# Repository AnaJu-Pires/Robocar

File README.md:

# Robocar Blitz

Carrinho autônomo seguidor de linha para a **RoboCar Race 2026, categoria Micro**. A pista tem linha preta de 20 mm sobre tapete claro, cruzamentos, interseções e bifurcações, e curvas de raio mínimo de 100 mm. Ao fim da volta, o robô tem de parar sozinho no box.
Inspeção e treino em **04/12/2026**; torneio em **05/12/2026** (SENAC Santo Amaro, São Paulo).

**Arquitetura:** câmera IMX219-160 → **Jetson Nano 4 GB** (visão + controle, Python) → USB serial → **ESP32** (PWM, encoders, bateria, largada, watchdog) → 2× DRV8833 → 2× N20 6 V (em 7,2 V). Detalhes em [docs/02_arquitetura.md](docs/02_arquitetura.md).

## Estado (09/11/2026)

| Parte | Situação |
|---|---|
| Software da Jetson | Implementado; **35 testes automáticos passando no PC**; integração com ESP32 **simulada** OK. Não testado na câmera real |
| Firmware da ESP32 | Implementado; **só checagem de sintaxe**, falta compilar e gravar |
| Hardware | Compras definidas (R$ 694,02 com fretes, dentro dos R$ 800); **pedidos a fazer** |
| Placa da ESP32 | **v0.8 espelhada** (motor esquerdo à esquerda, direito à direita; ESP32 no meio, USB para trás): 80 × 73 mm com furos M3 nos cantos, face simples (só B.Cu, sem vias), trilhas de 1,0/1,5 mm com gotas, **3 jumpers**; DRC 0 violações e paridade esquema × placa OK (`make drc`); **falta comprar barras fêmea e fenolite** ([lista de soldagem](hardware/placa_esp32/LISTA_DE_SOLDAGEM.md)), medir as peças, corroer e montar; chassi ainda na v0.7 ([hardware/placa_esp32/](hardware/placa_esp32/)) |
| Mecânica | **Chassi v4, 3 andares — é o que vamos cortar** (D-037): MDF 3 mm, 2 chapas de 390 × 270 mm, **176 × 143 × 181 mm** (162 mm com a câmera em 45°; furos de fixação gravados para furar à mão; luz em cima da câmera); XL4016 e bateria no piso, Jetson no 2º andar (portas para trás), ESP32 no 3º; 51 verificações automáticas (`make chassi`); curva R100 a no máximo 0,80 m/s (D-032); **cortar o pente primeiro** e conferir as medidas estimadas ([mecanica/chassi_v4/](mecanica/chassi_v4/)). Botão de desligar com LED ([hardware/placa_desligar/](hardware/placa_desligar/)) |

Próximos passos e cronograma: [docs/07_plano.md](docs/07_plano.md).

## Início rápido

```bash
make ajuda                      # lista os comandos
make testes                     # testes automáticos (PC ou Jetson; sem hardware)
make calibrar                   # na Jetson: calibração preto/branco
make visao                      # na Jetson: câmera ao vivo, sem mover motores
make carro PORTA=/dev/ttyUSB0   # no carro: largada pelo botão da ESP32
```
Instalação na Jetson: [jetson/README.md](jetson/README.md). Gravação da ESP32: [firmware/README.md](firmware/README.md).

## Onde está cada coisa

| Quero… | Vá para |
|---|---|
| entender a regra e o que perguntar à organização | [docs/01_regulamento.md](docs/01_regulamento.md) |
| ver componentes, elétrica, **pinagem**, massa e cálculos | [docs/03_hardware.md](docs/03_hardware.md) |
| entender ou alterar o código | [docs/04_software.md](docs/04_software.md) · [jetson/](jetson/) |
| ver o esquemático e a placa (PCB) da ESP32 | [hardware/placa_esp32/](hardware/placa_esp32/) |
| cortar e montar o chassi, fiação, inspeção | [mecanica/chassi_v4/](mecanica/chassi_v4/) |
| ver o protocolo Jetson ↔ ESP32 | [docs/05_protocolo_serial.md](docs/05_protocolo_serial.md) |
| testar (bancada e pista) e registrar resultados | [docs/06_testes.md](docs/06_testes.md) |
| comprar / ver orçamento e fretes | [compras/README.md](compras/README.md) |
| saber por que algo foi decidido | [docs/decisoes.md](docs/decisoes.md) |
| contribuir (convenções, git, checklist) | [CONTRIBUTING.md](CONTRIBUTING.md) |
| ver o código original | [legado/](legado/) |

```
docs/        documentação numerada + decisões + regulamento (PDF)
compras/     planilha de compras + CSV original
jetson/      software da Jetson: programas, biblioteca robocar/, config/, testes/
firmware/    firmware da ESP32 (Arduino)
hardware/    placa da ESP32 (KiCad: esquemático, PCB, arquivos de fabricação)
dados/       vídeos, logs e capturas dos testes (fora do git)
legado/      peb.py e seguir_linha.py originais, intactos
```

## Implementado
- Captura de baixa latência (GRAY8 no hardware, fila de 1 quadro, 60 fps, alternativas automáticas).
- Calibração salva em arquivo, com modo automático; limiar adaptativo à iluminação.
- Detecção por faixas que mantém a linha em cruzamentos e interseções em X; erro perto, erro longe e inclinação.
- Controle PD com antecipação e redução de velocidade em curva; busca e parada com linha perdida; parada opcional por marca.
- Protocolo serial versionado com checksum; firmware com estados, watchdog em dois níveis, rampa, encoders, bateria e botão de largada.
- Parâmetros com fonte única e validação; log CSV, gravação de vídeo e reprocessamento offline; Makefile; testes.

## Falta
- [ ] Compras, montagem e chassi.
- [ ] Compilar e testar o firmware; validar encoders, ADC e sentido dos motores.
- [ ] Testar a câmera real: modo, campo de visão, exposição, **latência**, tempo na Jetson.
- [ ] Controle de velocidade com encoder (PI na ESP32, protocolo v2).
- [ ] Ajustar ganhos e velocidades na pista de teste; definir a detecção do box conforme a resposta da organização.
- [x] Início automático no boot (`make servico`, em `jetson/servico/`). Falta testar na Jetson.
- [ ] Desligamento seguro sem SSH.

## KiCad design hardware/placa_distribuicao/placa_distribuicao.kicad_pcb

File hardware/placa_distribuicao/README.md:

# Placa de distribuição de energia (fusível, chave e saídas), 32 × 44 mm, face simples

Substitui a placa improvisada de cobre dividido. É a **mesma ideia** (cobre grande, fios soldados direto no cobre),
mas com 4 ilhas na ordem certa, um diodo de proteção e um LED de "chave ligada". Fica no **andar 2**, atrás da Jetson,
entre o plugue USB e o P4, em **2 espaçadores M3 de 10 mm**. Decisão: [D-036](../../docs/decisoes.md).

**Abrir no KiCad:** Arquivo → Abrir projeto → `hardware/placa_distribuicao/placa_distribuicao.kicad_pro`. Na janela
do projeto: esquemático (`placa_distribuicao.kicad_sch`) e placa (`placa_distribuicao.kicad_pcb`); na placa, **Alt+3**
abre o 3D. Abre no KiCad 7 a 10. O 3D também está em `placa_distribuicao.step` (abre no Onshape/FreeCAD). O
esquemático é conferido pelo próprio KiCad contra o circuito e contra a placa a cada `make placa-distribuicao`.

## Circuito

```
 XT60 (bateria) ── BAT+ ──[ F1 7 A ]── FUS+ ── fio ──► chave KCD1 (terminal 1)
                                                      chave KCD1 (terminal 2) ── fio ──► SW+
 SW+ ──► XL4016 #1 (Jetson)      um par de fios só para ele
     ──► XL4016 #2 (motores)     um par de fios só para ele
     ──► VBAT (fio fino até o J1 da placa da ESP32: medir a bateria)
     ──► R1 4,7 kΩ ──► LED verde ──► GND           aceso = chave ligada (puxa ~2 mA)
     ──┤◄── D1 1N5408 ── GND                       proteção contra bateria invertida
 XT60 (bateria) ── BAT− ── GND ──► XL4016 #1 −, XL4016 #2 −
```

| Ilha | Liga em | Fica |
|---|---|---|
| **BAT+** | + da bateria (pigtail do XT60) e um lado do fusível | trás, lado direito |
| **FUS+** | outro lado do fusível e o fio para o terminal 1 da chave | trás, lado esquerdo (perto da chave) |
| **SW+** | fio que volta do terminal 2 da chave; saídas XL1+, XL2+, VBAT; LED; catodo do D1 | frente, lado esquerdo |
| **GND** | − da bateria; XL1−, XL2−; LED; anodo do D1 | frente, lado direito |

## Por que assim (decisões)

| Pergunta | Decisão | Por quê |
|---|---|---|
| Ordem | **bateria → fusível → chave → conversores** | o fusível protege tudo a partir da bateria, inclusive o fio da chave. A placa improvisada não deixava claro onde a chave entrava |
| Como alimentar os 2 XL4016 | **um par de fios para cada um**, saindo da placa (em estrela) | antes o #2 pegava energia no borne do #1 (2 fios por borne). Com isso a corrente dos motores passava pelo borne e pelo fio da Jetson: quando os motores arrancavam, a entrada da Jetson também caía. Em estrela, cada um tem o seu fio |
| VBAT | **sai da placa** (ilha SW+), não emendado no terminal da chave | menos emenda; mede a bateria depois da chave, como antes |
| Diodo de proteção | **D1 em paralelo (catodo no SW+)**, não em série | em série, ele perderia ~0,5 V e esquentaria o tempo todo. Em paralelo, não faz nada no uso normal. Com a bateria invertida, ele conduz e **queima o fusível** antes de algo estragar (o XT60 já não encaixa invertido; isso cobre um pigtail soldado trocado ou uma fonte de bancada ligada ao contrário). Use **1N5408** (aguenta o pico até o fusível abrir); sem ele, 1N4007 é a segunda opção (pode abrir antes do fusível; aí só não protege) |
| LED verde | **aceso = chave ligada** | a Jetson desligada não mostra nada, e a bateria ligada com a chave esquecida em ON descarrega a LiPo abaixo do limite. O LED denuncia |
| Cobre | 4 ilhas grandes, **≥ 3 mm de largura em todo caminho** de corrente, pinos ligados **direto** (sem alívio térmico) | 7 A (fusível) em cobre de 35 µm pede ~2,5 mm (IPC-2221); 3 mm dá margem para a corrosão caseira. Ligação direta = mais corrente, como na placa improvisada (precisa de ferro de 40 W ou mais) |
| Sem letras no cobre | os nomes ficam na **folha de montagem** | letras de cobre partiam as ilhas no meio |
| Fixação | **2 parafusos M3 + espaçadores de 10 mm** | os fios são soldados por baixo: precisam de espaço até o MDF. Os furos ficam no vão entre as ilhas, com 3,6 mm sem cobre em volta (o parafuso não encosta em nenhuma ilha) |

## Peças (todas da lista de compras, exceto D1, LED e R1, do laboratório)

> **NUNCA use 1N4728 no D1.** O 1N4728 é um **zener de 3,3 V**, não um diodo retificador. No lugar do D1 ele
> conduz com qualquer tensão acima de 3,3 V: com a bateria (11–12,6 V) vira um **curto**, e o fusível queima (ou o
> zener esquenta até estourar) assim que a chave liga. Sem 1N5408 ou 1N400x, deixe o D1 vazio: a placa funciona igual,
> só sem a proteção contra bateria invertida (o XT60 já não encaixa ao contrário).

| Ref | Peça | Item da lista |
|---|---|---|
| F1 | fusível de vidro **5 × 20 mm 7 A** + 2 **terminais porta-fusível 5 × 20** (clipes para soldar) | 14 e 15 |
| — | chave gangorra **KCD1-101 2T** (na parede do berço da bateria, não na placa) | 16 |
| D1 | diodo **1N5408** (ou 1N4007; ver acima). **Sem eles, deixe o D1 vazio.** | laboratório / ~R$ 0,50 |
| D2 | LED verde 3 mm | laboratório |
| R1 | resistor 4,7 kΩ (3,3k a 10k servem) | laboratório |
| — | cabinho 0,75 mm² vermelho e preto | 19 e 20 |
| — | 2 espaçadores M3 de 10 mm + 2 parafusos M3 × 16 + porcas | 23 |
| — | placa de fenolite face simples, 32 × 44 mm (sobra da placa da ESP32) | — |

**Antes de corroer:** imprima `fabricacao/1_cobre_transferencia_1x1.pdf` em 100 % (sem "ajustar à página"), meça a
largura da placa no papel com régua (**32,0 mm**) e ponha os 2 clipes do fusível em cima do desenho. Os furos dos
clipes estão para clipes com pinos externos a **20 mm** (Littelfuse 111). Se os seus forem diferentes, me passem a
medida.

## Fazer

1. Corrosão: igual à placa da ESP32 (`1_cobre_transferencia_1x1.pdf`, preto = cobre, marca no centro de cada furo).
2. Furos: fios grossos 1,5 mm; clipes do fusível e D1 1,0–1,3 mm (confira na peça); R1, LED e VBAT 0,8–1,0 mm;
   fixação 3,2 mm. Mapa em `fabricacao/*.drl`.
3. Montagem pela [folha de montagem](fabricacao/2_montagem.pdf): clipes do fusível, D1 (**faixa no lado do SW+**),
   R1, LED (**perna longa no furo de cima, que vai ao R1**), fios por último.
4. **Antes de pôr a bateria**, multímetro em continuidade:
   * BAT+, FUS+, SW+ e GND **sem continuidade entre si** (sem o fusível);
   * com o fusível: BAT+ ↔ FUS+ em continuidade;
   * chave ligada: FUS+ ↔ SW+ em continuidade; desligada: aberto.
5. Bateria, chave desligada: LED apagado, 0 V nos XL4016. Chave ligada: LED aceso, tensão da bateria nos 2 XL4016.

## Fios (comprimentos de corte do modelo do chassi; ver `mecanica/chassi_v4/verificacao.md`)

| Fio | De → para | Corte |
|---|---|---|
| pigtail (vermelho + preto) | XT60 do chassi → BAT+ / BAT− | 132 mm |
| vermelho | CHAVE 1 → terminal 1 da chave | 92 mm |
| vermelho | terminal 2 da chave → CHAVE 2 | 93 mm |
| par | XL1 + / XL1 − → IN do XL4016 #1 (Jetson) | 151 mm |
| par | XL2 + / XL2 − → IN do XL4016 #2 (motores) | 145 mm |
| fino | VBAT → J1 da placa da ESP32 | 177 mm (Dupont de 1 via no meio, para tirar o andar 3) |

Os pares dos XL4016 descem pelo passa-fio novo na frente da placa (andar 2) e passam por cima dos motores.

## Gerar de novo

```bash
make placa-distribuicao
```

Roda `placa.py` (Python do KiCad): monta a placa, roda o DRC (cobre, furos, bordas, corpos, ligações), confere pino a
pino contra o circuito, confere que só há cobre embaixo e que todo caminho de corrente tem ≥ 3 mm, e grava o
`.kicad_pcb`, os PDFs 1:1, a furação e as imagens. `python3 placa.py --negativos` planta 8 defeitos (um deles, um esquemático com o diodo invertido) e confere
que cada um é pego.

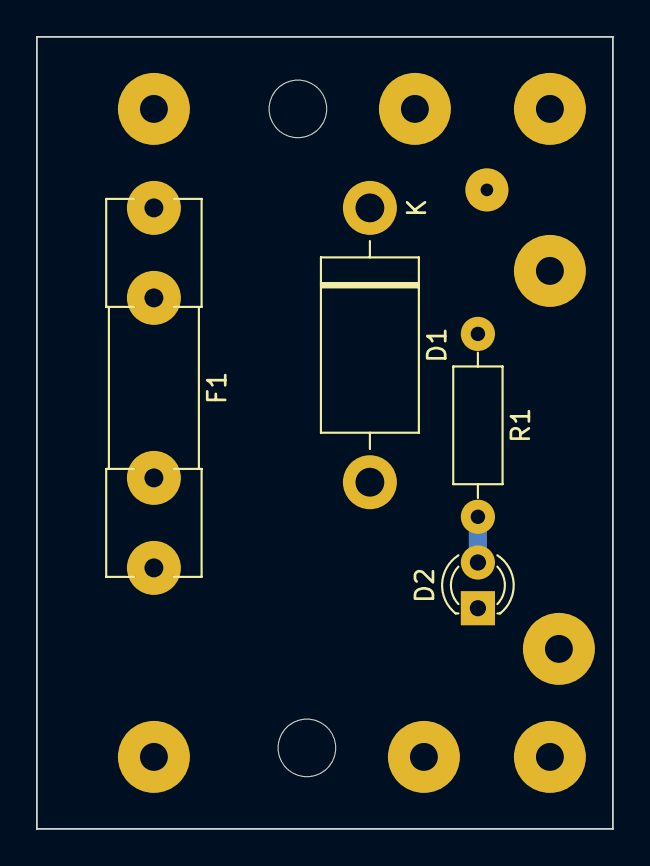
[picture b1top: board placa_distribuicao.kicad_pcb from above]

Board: 2 copper layers, 32.0 x 44.0 mm, 15 parts (0 on the bottom side), 5 nets.

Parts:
D1: D_DO-201AD_P15.24mm_Horizontal
D2: LED_D3.0mm
F1: Fuseholder_Clip-5x20mm_Littelfuse_111_Inline_P20.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; Fuseholder_Clip-5x20mm_Littelfuse_111_Inline_P20.00x5.00mm_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
H1, H2: MountingHole_3.2mm_M3
J_BATN: SolderWire-0.75sqmm_1x01_D1.25mm_OD2.3mm
J_BATP: SolderWire-0.75sqmm_1x01_D1.25mm_OD2.3mm
J_CH1, J_CH2: SolderWire-0.75sqmm_1x01_D1.25mm_OD2.3mm
J_VBAT: SolderWire-0.127sqmm_1x01_D0.48mm_OD1mm
J_XL1N, J_XL1P, J_XL2N, J_XL2P: SolderWire-0.75sqmm_1x01_D1.25mm_OD2.3mm
R1: R_Axial_DIN0207_L6.3mm_D2.5mm_P10.16mm_Horizontal

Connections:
BAT+: F1.2, J_BATP.1
FUS+: F1.1, J_CH1.1
GND: D1.2, D2.1, J_BATN.1, J_XL1N.1, J_XL2N.1
LED: D2.2, R1.2
SW+: D1.1, J_CH2.1, J_VBAT.1, J_XL1P.1, J_XL2P.1, R1.1

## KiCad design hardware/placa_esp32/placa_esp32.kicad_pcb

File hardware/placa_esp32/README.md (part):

# Robocar Blitz — placa da ESP32, v0.8 (espelhada)

Placa da ESP32 com os dois drivers DRV8833. **Tudo do motor esquerdo fica na metade esquerda da placa e tudo do
motor direito na metade direita**: cada cabo de motor (6 fios) e cada par de VM chega no seu lado. Face simples
(cobre só embaixo), para **corrosão manual**.

* **80 × 73 mm** (vista de cima: borda de cima = frente do carro, borda de baixo = traseira).
* **4 furos M3 nos cantos**, a 3,5 mm das bordas (73 × 66 mm entre centros). Nenhum cobre que não seja GND a menos
  de 3,6 mm do centro de um furo (pode usar espaçador metálico).
* **ESP32 em pé, no meio, com o USB para trás** (borda de baixo) e a antena para a frente. Embaixo da antena **não
  tem cobre** (área proibida no KiCad), como pede a Espressif — mesmo sem a ESP32 usar rádio neste projeto.
* **Ilhas retangulares arredondadas**, maiores só no sentido que não aproxima o pino vizinho (furo e passo das peças
  não mudaram — a ESP32 e os módulos continuam encaixando).
* **Trilhas**: sinal 1,0 mm; potência (VM, GND dos drivers e motores) 1,5 mm. Só 0°/45°/90°, **nenhuma curva de
  90°** (toda curva é chanfrada) e toda trilha **sai reta da ilha**, no sentido do lado comprido dela. Folga mínima
  0,5 mm (0,6 mm no plano de GND).
* **Gotas (teardrops)** em 64 saídas de ilha: o cobre engrossa na junção ilha–trilha (mais resistente ao calor do
  ferro e à corrosão por baixo).
* **Plano de GND** em volta de todas as ilhas; toda ilha de GND chega ao plano com pelo menos 2 raios de alívio
  térmico (sem toco de trilha).
* **3 jumpers de fio** (JP1, JP2 embaixo dos módulos e JP3 do lado do U3). Ver [Jumpers](#jumpers-3).
* Mesmo circuito da v0.7 (mais o JP3); **mudou a pinagem da ESP32** (firmware atualizado, [config.h](../../firmware/robocar_esp32/config.h)).

Lista do que soldar, o que é cada peça e o que já temos: **[LISTA_DE_SOLDAGEM.md](LISTA_DE_SOLDAGEM.md)**.

## O que tem aqui

| Arquivo | Conteúdo |
|---|---|
| `placa_esp32.kicad_pro` / `.kicad_sch` / `.kicad_pcb` | Projeto KiCad (abre no KiCad 10; arquivos no formato do KiCad 7, o KiCad 10 converte ao salvar) |
| `placa_esp32.kicad_dru` | Regras de **face simples** (DRC acusa trilha/zona em F.Cu e via) e as exceções de courtyard (resistores embaixo da ESP32) |
| `ferramentas/montar_placa_v08.py` | **Gera a placa** a partir do esquemático: posições, trilhas, plano, área da antena, gotas e serigrafia (tabelas `POS` e `ROTAS`) |
| `verificar.py` | DRC + "só B.Cu" + ângulos/larguras + distância aos furos + paridade esquema × placa + zona salva (`make drc`) |
| `gerar_saidas.sh` | Refaz PDFs, furação, STEP e imagens (`make placa`) |
| `placa_esp32.pdf` | Esquemático em PDF |
| `placa_esp32.step` | Placa montada em 3D (ESP32 do fabricante; barras fêmea, resistores e capacitores nativos do KiCad) |
| `fabricacao/1_cobre_transferencia_1x1.pdf` | **Arte do cobre**, 1:1 numa folha A4, preto = cobre, marca de centro nas ilhas |
| `fabricacao/2_montagem_e_jumpers.pdf` | Lado dos componentes: peças, referências e os 3 jumpers |
| `fabricacao/*.drl`, `*-drl_map.pdf` | Furação (Excellon) e mapa de brocas |
| `fabricacao/BOM.csv` | Peças com posição |
| `imagens/` | Cobre visto de cima, lado do cobre, folha de montagem e vista 3D |
| `lib/robocar_sm.pretty` | Pegadas `_SoldaManual` (ilhas retangulares arredondadas) |

## Disposição

| Lado ESQUERDO (motor esquerdo) | Meio | Lado DIREITO (motor direito) |
|---|---|---|
| J10 motor E (M+ M−), em cima | R1 + J1 (VBAT), em cima | J11 motor D (M+ M−), em cima |
| U2 = DRV8833 esquerdo | ESP32 (U1), USB para trás | U3 = DRV8833 direito, JP3 ao lado |
| J12 encoder E (A, B, −, +) | R2, R3, R4 embaixo da ESP32 | J13 encoder D (A, B, −, +); J14 largada |
| C1 470 µF + J2 VM E, embaixo | — | C2 470 µF + J3 VM D, embaixo |

* A **coluna esquerda** da ESP32 (pinos 1–15) só atende o motor esquerdo; a **direita** (16–30), o direito.
* Os sinais saem da coluna da ESP32 e sobem até as entradas do módulo (embaixo dele); as saídas (em cima) vão
  para J10/J11. VM e GND do módulo saem por dentro dele e descem pela borda até o 470 µF e o fio do XL4016.
* O 3V3 dos encoders sai do pino 3V3 (embaixo, coluna direita) pelos dois lados da ilha: um ramo vai direto ao J13
  e o outro passa por baixo da ponta USB da ESP32 até o J12.
* No J12/J13 a ordem é **A, B, −, +** (o + ficou na ponta para o 3V3 chegar sem cruzar nada; rótulos na serigrafia).

### Pinagem da ESP32 (igual ao [config.h](../../firmware/robocar_esp32/config.h))

| Pino | GPIO | Função | Vai para |
|---|---|---|---|
| 2 | 36 (VP) | bateria (ADC1) | R1 220k (VBAT) / R2 47k (GND) |
| 6 | 32 | nSLEEP do U2 | EEP do U2; R3 10k para o GND |
| 7 | 33 | motor esquerdo IN1 | IN2+IN4 do U2 (ponte espelhada, [D-013](../../docs/decisoes.md)) |
| 8 | 25 | motor esquerdo IN2 | IN1 do U2 e, pelo JP1, IN3 |
| 9 / 10 | 26 / 27 | encoder esquerdo A / B | J12 |
| 14 / 29 | GND | — | plano de GND |
| 20 | 21 | motor direito IN2 | IN1 do U3 e, pelo JP2, IN3 |
| 21 | 19 | motor direito IN1 | IN2+IN4 do U3 |
| 22 | 18 | nSLEEP do U3 | R4 10k para o GND e, pelo JP3, EEP do U3 |
| 24 / 25 | 17 / 16 | encoder direito A / B | J13 |
| 26 | 4 | largada | J14 (jumper ou botão para o GND) |
| 27 | 2 | LED | LED da própria DevKit |
| 30 | 3V3 | + dos encoders | J12, J13 |

Evitados: 0, 2, 5, 12, 15 (strapping), 1 e 3 (USB serial), 14 (PWM no boot), 39.

## Ligações (fios)

| Ponto | Fio | De onde |
|---|---|---|
| J2 `+ −` (VM E) | cabinho 0,75 mm² vermelho/preto | saída do **XL4016 #2 (7,2 V)** — 1º par |
| J3 `+ −` (VM D) | cabinho 0,75 mm² vermelho/preto | XL4016 #2 — 2º par |
| J10 `M+ M−` | vermelho (M+), branco (M−) | cabo do motor **esquerdo** |
| J12 `A B − +` | amarelo (A), verde (B), azul (−), preto (+) | **mesmo cabo** do motor esquerdo |
| J11 `M+ M−` | vermelho, branco | cabo do motor **direito** |
| J13 `A B − +` | amarelo, verde, azul, preto | mesmo cabo do motor direito |
| J1 `VBAT` | fio fino | + da bateria **depois da chave** |
| J14 | 2 pinos macho + jumper (ou botão em 2 fios) | largada |
| USB da ESP32 | cabo de dados | Jetson (alimenta a ESP32 e conversa com ela) |

Cores do cabo da RoboCore: 1 vermelho M+, 2 branco M−, 3 amarelo A, 4 verde B, 5 preto + do encoder, 6 azul − do
encoder. **Confira com o multímetro** antes de soldar.

## Regras usadas

| Item | Valor | Por quê |
|---|---|---|
| Trilha de sinal | **1,0 mm** | corrente de mA; 1,0 mm aguenta ≈ 2,4 A (IPC-2221, cobre 35 µm, +10 °C) e sobrevive à corrosão manual |
| VM, GND dos drivers, motores | **1,5 mm** | ≈ 3,2 A (IPC-2221, 35 µm, +10 °C) contra 1,9 A de pico (motor travado em 7,2 V): folga de 1,7× |
| Folga cobre–cobre | 0,5 mm (plano: 0,6 mm) | transferência térmica + percloreto |
| Cobre até a borda | ≥ 0,6 mm | |
| Ângulos | só 0°, 45° e 90° de direção; **nenhuma curva de 90°** (curvas chanfradas a 45°) | |
| Saída da ilha | reta, pelo lado comprido da ilha | |
| Gota (teardrop) | 90 % da largura da ilha → largura da trilha em 1,5 mm | |
| Alívio térmico | raios de 1,0 mm, folga 0,6 mm, ≥ 2 raios por ilha de GND | |

**Ilhas** (furo e passo originais):

| Peça | Furo | Ilha (retangular arredondada) |
|---|---|---|
| ESP32 e DRV8833 (barras fêmea) | 1,0 mm | 3,4 × 1,9 mm (cresce para fora da fileira; folga entre pinos igual: 0,64 mm) |
| Encoders e largada (J12, J13, J14) | 1,0 mm | 3,4 × 1,9 mm |
| Fios 0,75 mm² e motores (J1, J2, J3, J10, J11) | 1,55 mm | 3,6 × 4,2 mm (J1: 4 × 4 mm) |
| Resistores (passo 7,62 mm) | 0,8 mm | 3,0 × 2,4 mm |
| 470 µF (passo 3,5 mm) | 0,8 mm | 2,3 × 3,0 mm |
| Jumpers JP1–JP3 | 0,8 mm | 2,4 × 2,4 mm |

**Pino 1** (ilha com canto menos arredondado): + do eletrolítico, EN da ESP32, EEP dos DRV8833, M+ dos motores,
+ do VM, A dos encoders.

## Jumpers (3)

Fio rígido de 0,5–0,6 mm (perna cortada de resistor serve), deitado no lado dos componentes. Solde **antes** das
barras fêmea.

| # | Liga | Onde | Por quê |
|---|---|---|---|
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
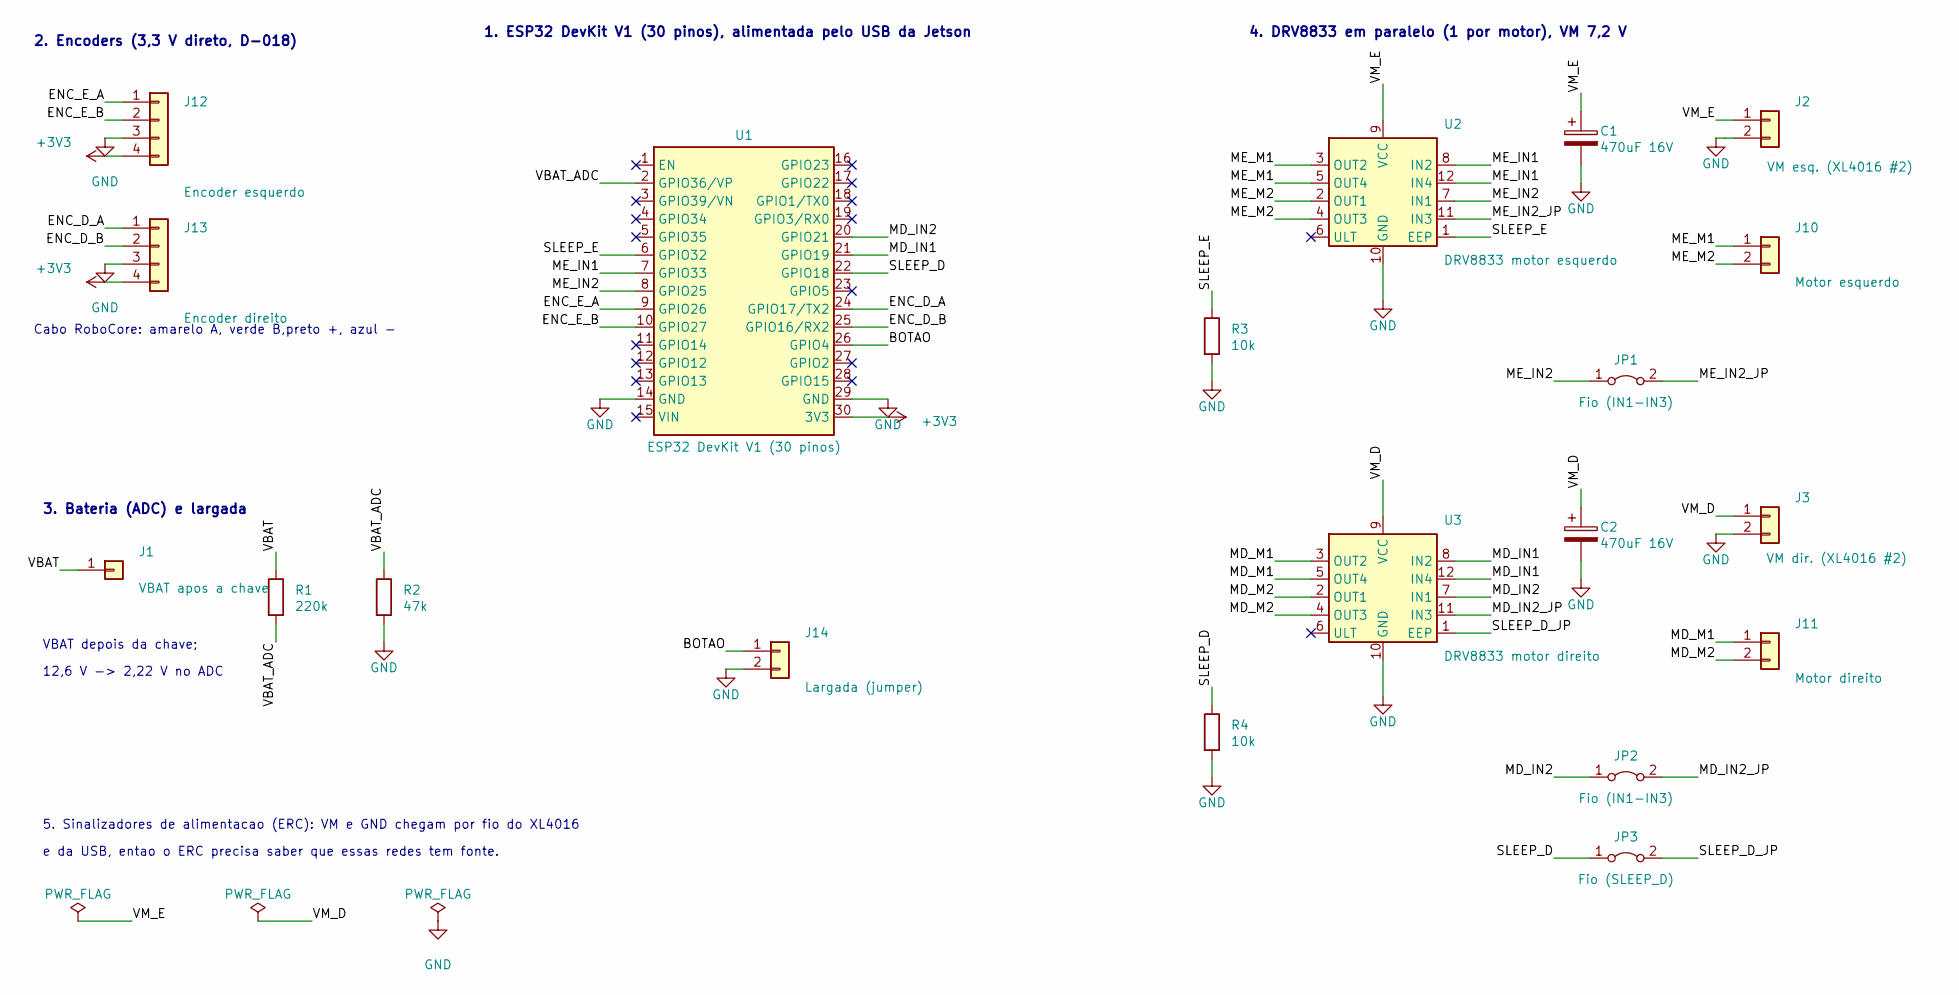
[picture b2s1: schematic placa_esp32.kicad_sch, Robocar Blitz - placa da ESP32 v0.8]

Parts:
C1, C2: 470uF 16V; CP_Radial_D8.0mm_P3.50mm_SoldaManual
J1: VBAT apos a chave; Fio_0.75mm2_1x01_SoldaManual
J2: VM esq. (XL4016 #2); Fio_0.75mm2_1x02_P4.8mm_SoldaManual
J3: VM dir. (XL4016 #2); Fio_0.75mm2_1x02_P4.8mm_SoldaManual
J10: Motor esquerdo; Fio_0.75mm2_1x02_P4.8mm_SoldaManual
J11: Motor direito; Fio_0.75mm2_1x02_P4.8mm_SoldaManual
J12: Encoder esquerdo; Fio_sinal_1x04_P2.54mm_SoldaManual
J13: Encoder direito; Fio_sinal_1x04_P2.54mm_SoldaManual
J14: Largada (jumper); Fio_sinal_1x02_P2.54mm_SoldaManual
JP1, JP2: Fio (IN1-IN3); Jumper_Fio_P10.16mm_SoldaManual
JP3: Fio (SLEEP_D); Jumper_Fio_P10.16mm_SoldaManual
R1: 220k; R_Axial_DIN0207_P7.62mm_SoldaManual
R2: 47k; R_Axial_DIN0207_P7.62mm_SoldaManual
R3, R4: 10k; R_Axial_DIN0207_P7.62mm_SoldaManual
U1: ESP32 DevKit V1 (30 pinos); ESP32_DevKit_V1_30p_SoldaManual
U2: DRV8833 motor esquerdo; DRV8833_Modulo_SoldaManual
U3: DRV8833 motor direito; DRV8833_Modulo_SoldaManual

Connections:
+3V3: J12.4, J13.4, U1.30 (3V3)
/BOTAO: J14.1, U1.26 (GPIO4)
/ENC_D_A: J13.1, U1.24 (GPIO17/TX2)
/ENC_D_B: J13.2, U1.25 (GPIO16/RX2)
/ENC_E_A: J12.1, U1.9 (GPIO26)
/ENC_E_B: J12.2, U1.10 (GPIO27)
/MD_IN1: U1.21 (GPIO19), U3.8 (IN2), U3.12 (IN4)
/MD_IN2: JP2.1 (A), U1.20 (GPIO21), U3.7 (IN1)
/MD_IN2_JP: JP2.2 (B), U3.11 (IN3)
/MD_M1: J11.1, U3.3 (OUT2), U3.5 (OUT4)
/MD_M2: J11.2, U3.2 (OUT1), U3.4 (OUT3)
/ME_IN1: U1.7 (GPIO33), U2.8 (IN2), U2.12 (IN4)
/ME_IN2: JP1.1 (A), U1.8 (GPIO25), U2.7 (IN1)
/ME_IN2_JP: JP1.2 (B), U2.11 (IN3)
/ME_M1: J10.1, U2.3 (OUT2), U2.5 (OUT4)
/ME_M2: J10.2, U2.2 (OUT1), U2.4 (OUT3)
/SLEEP_D: JP3.1 (A), R4.1, U1.22 (GPIO18)
/SLEEP_D_JP: JP3.2 (B), U3.1 (EEP)
/SLEEP_E: R3.1, U1.6 (GPIO32), U2.1 (EEP)
/VBAT: J1.1, R1.1
/VBAT_ADC: R1.2, R2.1, U1.2 (GPIO36/VP)
/VM_D: C2.1, J3.1, U3.9 (VCC)
/VM_E: C1.1, J2.1, U2.9 (VCC)
GND: C1.2, C2.2, J2.2, J3.2, J12.3, J13.3, J14.2, R2.2, R3.2, R4.2, U1.14 (GND), U1.29 (GND), U2.10 (GND), U3.10 (GND)

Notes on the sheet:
12,6 V -> 2,22 V no ADC
VBAT depois da chave;
1. ESP32 DevKit V1 (30 pinos), alimentada pelo USB da Jetson
2. Encoders (3,3 V direto, D-018)
3. Bateria (ADC) e largada
preto +, azul -
4. DRV8833 em paralelo (1 por motor), VM 7,2 V
Cabo RoboCore: amarelo A, verde B,
5. Sinalizadores de alimentacao (ERC): VM e GND chegam por fio do XL4016
e da USB, entao o ERC precisa saber que essas redes tem fonte.

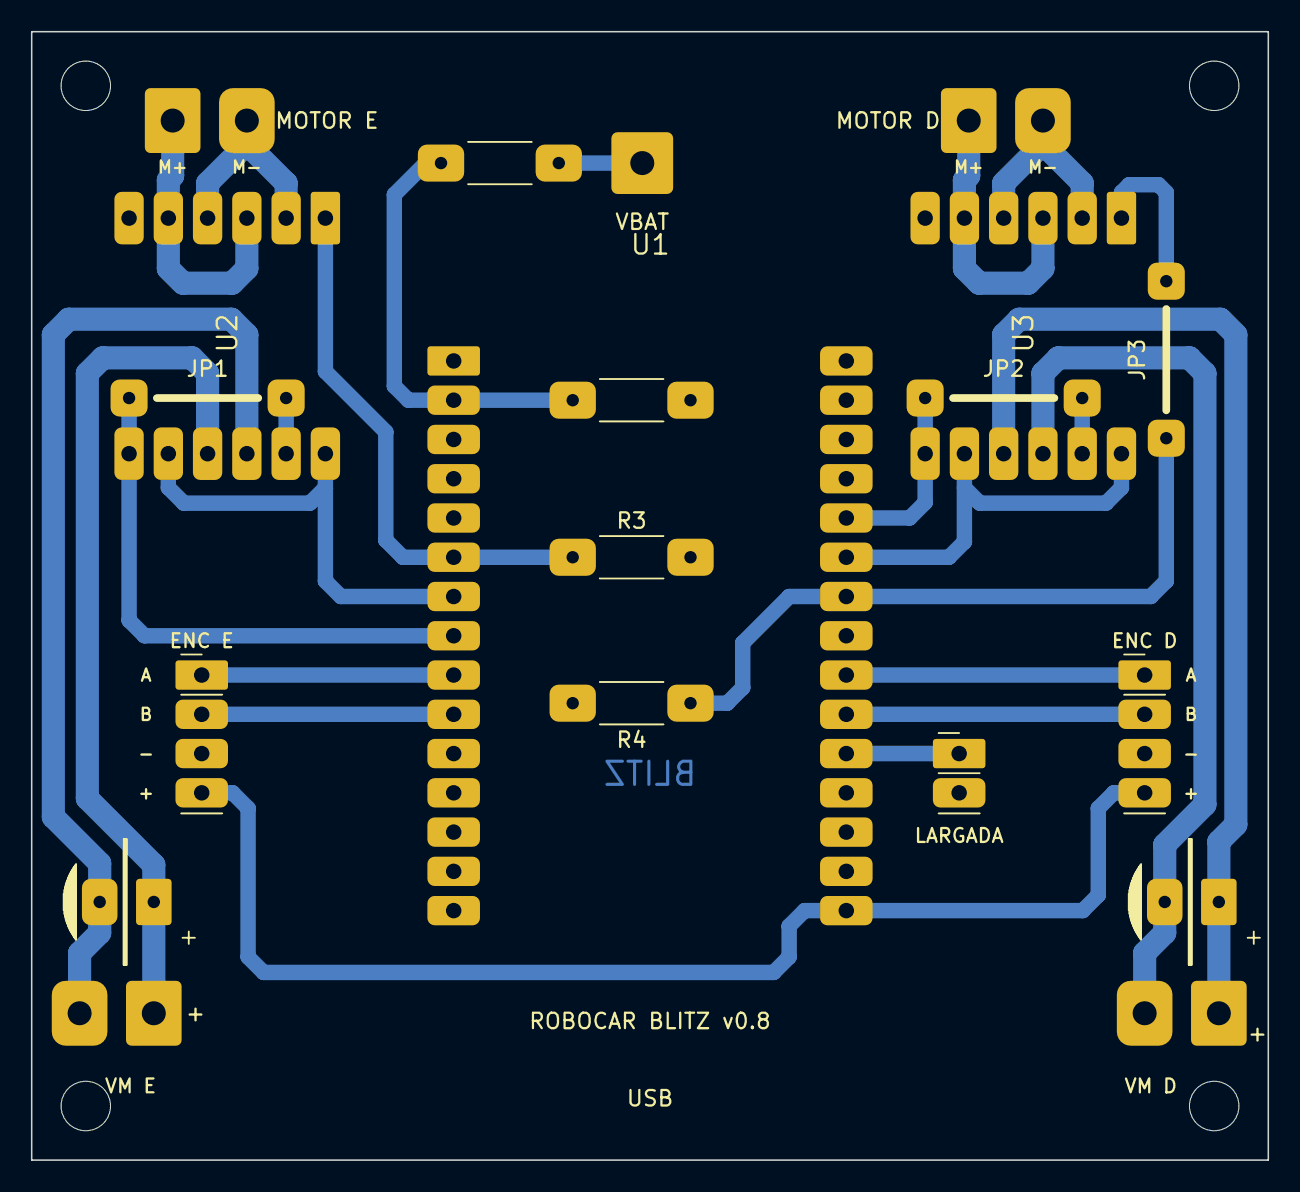
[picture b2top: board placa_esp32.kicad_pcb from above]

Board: 2 copper layers, 80.0 x 73.0 mm, 24 parts (0 on the bottom side), 24 nets.

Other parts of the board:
H1, H2, H3, H4: MountingHole_3.2mm_M3

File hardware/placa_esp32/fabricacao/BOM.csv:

Ref,Valor,Pegada,X (mm),Y (mm),Rotacao,Origem / observacao
C1,470uF 16V,CP_Radial_D8.0mm_P3.50mm_SoldaManual,7.9,56.3,180,"Smart Kits (4 comprados); medir diametro e passo das pernas: pegada = 8 mm, passo 3,5 mm"
C2,470uF 16V,CP_Radial_D8.0mm_P3.50mm_SoldaManual,76.8,56.3,180,idem
J1,VBAT apos a chave,Fio_0.75mm2_1x01_SoldaManual,39.5,8.5,0,fio fino do + da bateria depois da chave
J2,VM esq. (XL4016 #2),Fio_0.75mm2_1x02_P4.8mm_SoldaManual,7.9,63.5,180,"par de cabinho 0,75 mm2 do XL4016 #2 (7,2 V)"
J3,VM dir. (XL4016 #2),Fio_0.75mm2_1x02_P4.8mm_SoldaManual,76.8,63.5,180,"idem, segundo par"
J10,Motor esquerdo,Fio_0.75mm2_1x02_P4.8mm_SoldaManual,9.12,5.75,0,fios vermelho (M+) e branco (M-) do motor esquerdo
J11,Motor direito,Fio_0.75mm2_1x02_P4.8mm_SoldaManual,60.62,5.75,0,"idem, motor direito"
J12,Encoder esquerdo,Fio_sinal_1x04_P2.54mm_SoldaManual,11,41.62,0,"fios amarelo (A), verde (B), azul (-), preto (+) do encoder esquerdo"
J13,Encoder direito,Fio_sinal_1x04_P2.54mm_SoldaManual,72,41.62,0,"idem, encoder direito"
J14,Largada (jumper),Fio_sinal_1x02_P2.54mm_SoldaManual,60,46.7,0,barra de pinos macho 1x2 + jumper (sobra do pacote J48) ou botao em 2 fios
JP1,Fio (IN1-IN3),Jumper_Fio_P10.16mm_SoldaManual,6.3,23.7,0,"fio rigido 0,5-0,6 mm deitado embaixo do U2 (soldar antes das barras femea)"
JP2,Fio (IN1-IN3),Jumper_Fio_P10.16mm_SoldaManual,57.8,23.7,0,"idem, embaixo do U3"
JP3,Fio (SLEEP_D),Jumper_Fio_P10.16mm_SoldaManual,73.4,26.3,90,"fio rigido 0,5-0,6 mm em pe, a direita do U3"
R1,220k,R_Axial_DIN0207_P7.62mm_SoldaManual,34.1,8.5,180,laboratorio (L08)
R2,47k,R_Axial_DIN0207_P7.62mm_SoldaManual,35,23.84,0,laboratorio (L08); fica embaixo da ESP32: soldar antes das barras femea
R3,10k,R_Axial_DIN0207_P7.62mm_SoldaManual,35,34,0,laboratorio; embaixo da ESP32
R4,10k,R_Axial_DIN0207_P7.62mm_SoldaManual,42.62,43.44,180,laboratorio; embaixo da ESP32
U1,ESP32 DevKit V1 (30 pinos),ESP32_DevKit_V1_30p_SoldaManual,27.3,21.3,0,ja temos; encaixa em 2 barras femea 1x15 (comprar)
U2,DRV8833 motor esquerdo,DRV8833_Modulo_SoldaManual,19,12.06,-90,Smart Kits; encaixa em 2 barras femea 1x6 (comprar)
U3,DRV8833 motor direito,DRV8833_Modulo_SoldaManual,70.5,12.06,-90,idem

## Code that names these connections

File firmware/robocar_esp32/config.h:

// =====================================================================================
// Robocar Blitz - configuracao do firmware da ESP32 (pinos e constantes)
// Fonte unica da pinagem: docs/03_hardware.md reproduz esta tabela.
// =====================================================================================
#pragma once

// ----- Protocolo (deve ser igual a jetson/robocar/protocolo.py: VERSAO) --------------
#define PROTOCOLO_VERSAO 2   // v2: flag DESLIGAR (botao segurado) na telemetria

// ----- Pinagem (ESP32 DevKit) -------------------------------------------------------
// Placa v0.8 (hardware/placa_esp32, D-024): placa ESPELHADA. A coluna esquerda da ESP32 (EN...VIN)
// atende so o motor ESQUERDO e a coluna direita (GPIO23...3V3) so o motor DIREITO, para que tudo do
// motor esquerdo fique na metade esquerda da placa e tudo do direito na metade direita.
// Pinos evitados: strapping (0, 2, 5, 12, 15), TX/RX (1, 3), 14 (PWM no boot) e 39.
// DRV8833 em modo paralelo, um modulo por motor (IN1+IN3 juntos, IN2+IN4 juntos).
// Ponte ESPELHADA (D-013): PIN_x_IN1 vai em IN2+IN4 do modulo e o M+ do motor sai de OUT2+OUT4.
// A tabela-verdade do DRV8833 e simetrica: IN1=1/IN2=0 continua sendo "M+ positivo".
const int PIN_ME_IN1 = 33;   // motor esquerdo: IN2+IN4 do modulo esquerdo (U2)       [pino 7 da DevKit]
const int PIN_ME_IN2 = 25;   // motor esquerdo: IN1+IN3                                [pino 8]
const int PIN_MD_IN1 = 19;   // motor direito:  IN2+IN4 do modulo direito (U3)         [pino 21]
const int PIN_MD_IN2 = 21;   // motor direito:  IN1+IN3                                [pino 20]
const int PIN_SLEEP_E = 32;  // EEP (nSLEEP) do modulo esquerdo; pull-down de 10k. HIGH = ligado [pino 6]
const int PIN_SLEEP_D = 18;  // EEP (nSLEEP) do modulo direito;  pull-down de 10k     [pino 22]
const int PIN_ENC_E_A = 26;  // encoder esquerdo, alimentado em 3,3 V (D-018)         [pino 9]
const int PIN_ENC_E_B = 27;  //                                                       [pino 10]
const int PIN_ENC_D_A = 17;  // encoder direito, idem                                 [pino 24]
const int PIN_ENC_D_B = 16;  //                                                       [pino 25]
const int PIN_VBAT   = 36;   // ADC1: divisor 220k (topo) / 47k (baixo)               [pino 2]
const int PIN_BOTAO  = 4;    // largada: BOTAO para o GND, INPUT_PULLUP (jumper fixo nao: pediria desligar)   [pino 26]
const int PIN_BUZZER = -1;   // sem buzzer na placa (-1 = desligado)
const int PIN_LED    = 2;    // LED da propria DevKit

// ----- Motores ----------------------------------------------------------------------
const bool INVERTER_E = true;       // T05 (21/11): com false/true as duas rodas giravam ao contrario
const bool INVERTER_D = false;      // motores espelhados: normalmente um e invertido
const uint32_t PWM_FREQ = 20000;    // 20 kHz: fora da faixa audivel
const uint8_t  PWM_BITS = 10;
const int      DUTY_MAX_PCT = 100;  // VM regulado em 7,2 V pelo XL4016 #2 (D-019): 100% = 7,2 V no motor
const int      RAMPA_POR_MS = 10;   // unidades (de 1000) por ms: 0 -> 100% em 100 ms

// ----- Seguranca --------------------------------------------------------------------
const uint32_t WATCHDOG_FREIO_MS   = 250;   // sem comando: freia (continua armado)
const uint32_t WATCHDOG_DESARME_MS = 1000;  // sem comando: desarma (exige novo botao)
const uint32_t TELEMETRIA_MS = 20;          // 50 Hz
const uint32_t BOTAO_DESLIGAR_MS = 3000;    // botao segurado (com o robo parado): pede a Jetson para desligar
const uint32_t DESLIGAR_AVISO_MS = 3000;    // por quanto tempo a flag DESLIGAR fica ligada na telemetria
// Depois do pedido, a Jetson fecha o programa (a ESP32 fica sem comandos e vai para SEM_JETSON) e o Linux desliga.
// ESPERA_DESLIGAR_MS depois de a Jetson sumir, o LED faz 2 piscadas por segundo = "pode desligar a chave".
// Medir no T15 quanto o desligamento demora e deixar uma folga (D-039). Se os comandos voltarem, cancela.
#ifndef ESPERA_DESLIGAR_MS_SIM
const uint32_t ESPERA_DESLIGAR_MS = 25000;
#else
const uint32_t ESPERA_DESLIGAR_MS = ESPERA_DESLIGAR_MS_SIM;   // simulacao no PC (firmware/simulacao): mais curto
#endif
const uint32_t DESLIGAR_SEM_RESPOSTA_MS = 5000;  // a Jetson continuou mandando comandos: nao desligou, cancela

// ----- Bateria 3S -------------------------------------------------------------------
const float DIVISOR_VBAT = (220.0f + 47.0f) / 47.0f;   // 12,6 V -> 2,22 V no pino
const int   VBAT_AVISO_MV = 9900;           // 3,3 V/celula: aviso na telemetria (e buzzer, se houver)
const int   VBAT_CORTE_MV = 9600;           // 3,2 V/celula por 2 s: FALHA_BATERIA
const int   VBAT_MINIMA_VALIDA_MV = 5000;   // abaixo disso: divisor desligado (bancada via USB)

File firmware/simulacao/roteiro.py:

"""Jetson (robocar/esp32.py, protocolo.py e controle.py reais) conversando com o firmware da ESP32 simulado no PC.

    make sim-esp32        (na raiz do repositorio; precisa de g++ e Python 3, Linux ou macOS)

O firmware (firmware/robocar_esp32) e compilado com um Arduino falso (inc/Arduino.h + sim.cpp): a serial vira
stdin/stdout, os pinos viram um registro de eventos e o botao, a bateria e os encoders sao arquivos em estado/.
Nao substitui o teste na placa (docs/06_testes.md), mas pega erro de logica, de protocolo e de pinagem.
"""
import os, sys, time, subprocess, fcntl
AQUI = os.path.dirname(os.path.abspath(__file__))
os.chdir(AQUI)
sys.path.insert(0, os.path.join(AQUI, '..', '..', 'jetson'))
from robocar import protocolo
from robocar.esp32 import LinkESP32
from robocar.controle import Controlador
from robocar import configuracao

SIM = os.path.abspath('estado'); os.makedirs(SIM, exist_ok=True)
for f in os.listdir(SIM): os.remove(os.path.join(SIM, f))
def setf(n, v):
    tmp = os.path.join(SIM, n + '.tmp'); open(tmp, 'w').write(str(v)); os.replace(tmp, os.path.join(SIM, n))
setf('botao', 1); setf('pino36_mv', 0)
log = open('eventos.log', 'w')
p = subprocess.Popen(['build/esp_sim'], stdin=subprocess.PIPE, stdout=subprocess.PIPE, stderr=log, env=dict(os.environ, SIMDIR=SIM))
fcntl.fcntl(p.stdout, fcntl.F_SETFL, os.O_NONBLOCK)

class Ser:
    buf = b''
    @property
    def in_waiting(self):
        try:
            d = os.read(p.stdout.fileno(), 65536)
            if d: self.buf += d
        except BlockingIOError: pass
        return len(self.buf)
    def read(self, n): d, self.buf = self.buf[:n], self.buf[n:]; return d
    def write(self, d): p.stdin.write(d); p.stdin.flush()
    def close(self): pass

link = LinkESP32(Ser()); link.pedir_versao()
ok = []
def check(nome, cond, extra=''):
    ok.append(cond); print(('OK   ' if cond else 'FALHA'), nome, extra)
def rodar(seg, cmd=None, extra=None):
    t1 = time.time() + seg
    while time.time() < t1:
        if cmd: link.enviar_motores(*cmd)
        if extra: extra()
        link.ler(); time.sleep(0.02)
    return link.telemetria
def eventos():
    log.flush(); return [l.split() for l in open('eventos.log')]
def ultimo_pwm():
    v = {}
    for e in eventos():
        if e[1] == 'PWM': v[int(e[2])] = int(e[3])
    return v
def subidas(pino, desde_ms):
    """Quantas vezes o pino foi para 1 a partir de 'desde_ms' (tempo do firmware)."""
    return sum(1 for e in eventos() if e[1] == 'DW' and int(e[2]) == pino and int(e[3]) == 1 and int(e[0]) >= desde_ms)
def nivel(pino):
    v = None
    for e in eventos():
        if e[1] == 'DW' and int(e[2]) == pino: v = int(e[3])
    return v

t = rodar(0.4)
check('responde a versao do protocolo', link.versao_firmware == protocolo.VERSAO, link.versao_firmware)
check('liga em SEM_JETSON, drivers dormindo', t['estado'] == protocolo.SEM_JETSON and nivel(32) == 0 and nivel(18) == 0)
check('PWM a 20 kHz, 10 bits, nos 4 pinos 33/25/19/21', sorted(int(e[2]) for e in eventos() if e[1] == 'LEDC') == [19, 21, 25, 33])
t = rodar(0.3, (0, 0))
check('com comandos da Jetson -> PRONTO', t['estado'] == protocolo.PRONTO)
check('PRONTO nao liga o driver', nivel(32) == 0 and nivel(18) == 0)
# largada pelo J14 (jumper/botao para o GND)
setf('botao', 0); t = rodar(0.1, (0, 0)); setf('botao', 1); t = rodar(0.2, (0, 0))
check('botao de largada (J14) -> ARMADO', t['estado'] == protocolo.ARMADO)
check('ARMADO acorda os dois drivers (GPIO32 e GPIO18 em 1)', nivel(32) == 1 and nivel(18) == 1)
# lado da Jetson: controlador inicia na borda de armado
cfg = configuracao.carregar_config(None, {})
ctrl = Controlador(cfg['controle'], cfg['parada']); ctrl.iniciar(time.time())
det = {'erro': 0.0, 'erro_longe': 0.0, 'marca': False}
e, d, info = ctrl.atualizar(det, time.time() + 1.0)   # depois da rampa de largada (controle.acel_max)
check('controle com a linha no centro -> as duas rodas para frente iguais', e > 0 and abs(e - d) < 1e-9, '(%.2f, %.2f)' % (e, d))
t = rodar(0.4, (e, d))
pw = ultimo_pwm(); duty = int(round(e * 1000)) * 1023 // 1000
check('motor esquerdo (INVERTER_E): GPIO25=1023 e GPIO33 com PWM (frente)', pw[25] == 1023 and pw[33] == 1023 - duty, pw)
check('motor direito: GPIO19=1023 e GPIO21 com PWM', pw[19] == 1023 and pw[21] == 1023 - duty, pw)
e, d, _ = ctrl.atualizar({'erro': 0.5, 'erro_longe': 0.5, 'marca': False}, time.time() + 1.05)
check('linha a direita -> roda esquerda mais rapida', e > d, '(%.2f, %.2f)' % (e, d))
# encoders
setf('enc_e', 140); setf('enc_d', -140); t = rodar(0.2, (e, d))
check('encoders contados (x4) e chegam na telemetria', abs(t['enc_e']) == 140 and abs(t['enc_d']) == 140, (t['enc_e'], t['enc_d']))
# bateria: 12,6 V -> 2,22 V no pino
setf('pino36_mv', round(12600 * 47 / 267)); t = rodar(1.5, (e, d))
check('bateria 12,6 V medida pelo divisor 220k/47k', abs(t['vbat'] - 12.6) < 0.05, t['vbat'])
# watchdog
t = rodar(0.4)
check('Jetson parou de mandar: freia (flag watchdog), ainda armado', t['estado'] == protocolo.ARMADO and t['flags'] & 1 and ultimo_pwm()[33] == 1023 and ultimo_pwm()[25] == 1023)
t = rodar(1.0)
check('sem Jetson por 1 s: desarma e drivers dormem', t['estado'] == protocolo.SEM_JETSON and nivel(32) == 0 and nivel(18) == 0)
# armar pela Jetson ($A, modo bancada) e parar ($S)
t = rodar(0.3, (0, 0)); link.armar(); t = rodar(0.2, (0, 0))
check('$A (bancada) arma', t['estado'] == protocolo.ARMADO)
link.parar(); t = rodar(0.2, (0, 0))
check('$S desarma (fim de prova)', t['estado'] == protocolo.PRONTO)
# botao: armado, apertar para na hora (sem esperar soltar) e soltar nao arma de novo
link.armar(); t = rodar(0.2, (0.3, 0.3))
setf('botao', 0); t = rodar(0.15, (0.3, 0.3))
check('botao apertado com o robo armado -> para na hora', t['estado'] == protocolo.PRONTO and nivel(32) == 0)
setf('botao', 1); t = rodar(0.2, (0, 0))
check('soltar depois de parar nao arma de novo', t['estado'] == protocolo.PRONTO)
# botao segurado 3 s com o robo parado -> flag DESLIGAR, sem armar
setf('botao', 0); t = rodar(1.0, (0, 0))
check('segurando o botao: ainda nao arma nem pede desligar', t['estado'] == protocolo.PRONTO and not t['desligar'])
t = rodar(2.3, (0, 0))
check('segurado 3 s -> flag DESLIGAR na telemetria (protocolo v2)', t['desligar'] and t['estado'] == protocolo.PRONTO, t['flags'])
setf('botao', 1); t = rodar(0.3, (0, 0))
check('soltar depois do pedido de desligar nao arma', t['estado'] == protocolo.PRONTO)
t = rodar(3.2, (0, 0))
check('flag DESLIGAR some depois de 3 s', not t['desligar'], t['flags'])
# sequencia completa de desligar (D-039): LED da ESP32 (GPIO2) diz quando pode cortar a chave
t = rodar(5.0, (0, 0))       # a Jetson continuou mandando (8 s apos o pedido): nao desligou -> cancela
m0 = t['ms']; t = rodar(2.0, (0, 0))
check('Jetson nao obedeceu ao desligar: LED volta ao normal (PRONTO, 1 piscada/s)', subidas(2, m0) <= 3, subidas(2, m0))
setf('botao', 0); t = rodar(3.3, (0, 0)); setf('botao', 1)
check('novo pedido de desligar', t['desligar'], t['flags'])
rodar(1.3)                   # a Jetson fechou o programa: sem comandos
m0 = link.telemetria['ms']; t = rodar(0.5)
check('Jetson sumiu: SEM_JETSON e LED pisca muito rapido (ainda NAO desligar)', t['estado'] == protocolo.SEM_JETSON and subidas(2, m0) >= 4, subidas(2, m0))
rodar(1.6)                   # ESPERA_DESLIGAR_MS = 2 s na simulacao (25 s na placa)
m0 = link.telemetria['ms']; t = rodar(2.0)
n = subidas(2, m0)
check('depois da espera: 2 piscadas por segundo = pode desligar a chave', 3 <= n <= 5, n)
t = rodar(0.3, (0, 0)); m0 = t['ms']; t = rodar(2.0, (0, 0))
check('Jetson voltou a mandar comandos: cancela e volta a PRONTO (1 piscada/s)', t['estado'] == protocolo.PRONTO and subidas(2, m0) <= 3, subidas(2, m0))
# bateria baixa
link.armar(); rodar(0.2, (0.3, 0.3))
setf('pino36_mv', round(9300 * 47 / 267)); t = rodar(4.5, (0.3, 0.3))
check('bateria < 9,6 V por 2 s -> FALHA_BATERIA e motores desligados', t['estado'] == protocolo.FALHA_BATERIA and nivel(32) == 0, (t['vbat'], t['estado']))
link.armar(); t = rodar(0.3, (0.3, 0.3))
check('em FALHA_BATERIA nao arma de novo', t['estado'] == protocolo.FALHA_BATERIA)
check('nenhuma linha invalida recebida', link.linhas_invalidas == 0, link.linhas_invalidas)
p.kill()
print('\n%d/%d OK' % (sum(ok), len(ok)))
sys.exit(0 if all(ok) else 1)
